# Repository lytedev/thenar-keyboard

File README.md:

# Thenar

A column-staggered, fully-wireless split keyboard with scrollwheels — 56 keys (28 per half + thumb cluster). Choc-spaced, hotswap, Nice!Nano + ZMK.

## Repositories

- **Primary**: <https://git.lyte.dev/lytedev/thenar-keyboard>
- **Mirror (GitHub)**: <https://github.com/lytedev/thenar-keyboard>
- **Sibling model**: [hypothenar](https://git.lyte.dev/lytedev/hypothenar-keyboard) — the pick-and-place (JLCPCB PCBA) sibling: same layout, completely different electronics ([GitHub mirror](https://github.com/lytedev/hypothenar-keyboard))

- Choc-spaced, hot-swappable
- Scrollwheel (`EVQWGD001`) on both sides
- Strong pinky stagger (0.66) and a 5 deg. pinky splay
- Fully wireless built for Nice!Nano + ZMK (no TRRS jack)
- Nice!View support (5 pin connector)
- Reversible PCB
- 3d printable magnetic case, switchplate and MCU cover

## Gallery

TODO: Take photos of the assembled Thenar and add them here.

## Firmware

Natively supports [ZMK](https://zmk.dev/). Build + flash via the flake:

```sh
nix build .#firmware             # both halves
nix run .#flash -- left          # build + flash (double-tap reset when prompted)
nix run .#flash -- right
```

The shield definition + keymap live in [`config/`](./config/).
See `config/README.md` for the full firmware development workflow,
including hash-pinning the Zephyr SDK on first build.

## Build guide

[see the docs](./docs/) — [build](./docs/build.md), [routing](./docs/routing.md). Both are LLM-drafted and unverified; treat them as starting points until someone has built and routed a Thenar end-to-end.

## Development

The build has two phases:

1. **Ergogen produces a scaffold** — KiCad PCBs with all the footprints
   placed and nets assigned, but **no copper routing**. This is the
   starting point.
2. **A human routes the scaffold in KiCad by hand** and commits the
   result to `thenar/routed/`. Gerbers are then exported from the
   committed routed file, not from the ergogen scaffold.

This is unavoidable: ergogen is a layout generator, not an autorouter, and
a useful keyboard PCB needs every net wired up by hand to fit two layers.

### Flake packages

```sh
nix build .#scaffold          # ergogen -> KiCad PCBs (UNROUTED, for hand-routing)
nix build .#gerbers           # gerbers from thenar/routed/keyboard.kicad_pcb
nix build .#gerbers-zip       # ^^ zipped, ready to upload to JLCPCB etc. (default)
nix build .#switchplate-step  # STEP model of the switchplate (1.2mm)
nix flake check               # verifies thenar/routed/ placement matches scaffold
```

Each `result` symlink points at the artifact in `/nix/store`. For an
interactive shell with `ergogen`, `kicad-cli`, and `zip` available:

```sh
nix develop
```

### The two paths to fab-ready gerbers

- **Use the committed routed PCB.** `nix build .#gerbers-zip` and upload
  the result. This is the default path and the only one that has a chance
  of working without you doing any routing yourself.
- **Route your own.** Run `nix build .#scaffold`, open
  `result/pcbs/keyboard.kicad_pcb` in KiCad, route every net, save the
  routed file over `thenar/routed/keyboard.kicad_pcb`, then
  `nix build .#gerbers-zip`. If you fork the repo, commit your routed
  PCB so anyone using your fork gets it for free.

`nix flake check` runs `check-routing-drift`, which compares footprint
placement between the freshly-generated scaffold and the committed
`thenar/routed/` PCB. If you edit `thenar/ergogen/config.yaml` without
re-merging into the routed file, this check will fail loudly.

## License

MIT — see [LICENSE](LICENSE).

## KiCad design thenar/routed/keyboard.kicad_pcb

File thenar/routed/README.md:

# Routed PCB

This directory holds the **manually-routed** KiCad PCBs that gerbers are built
from. Ergogen places footprints and assigns nets, but does not route copper —
that step has to be done by hand in KiCad. The result of that hand-routing
lives here and is committed.

## Workflow

1. `nix build .#pcbs` produces the ergogen scaffold (footprints + nets, no
   traces) at `result/pcbs/keyboard.kicad_pcb`.
2. The first time, that scaffold is copied verbatim into this directory as a
   seed. You then open it in KiCad and route the traces by hand. Commit the
   routed file.
3. `nix build .#gerbers` reads the routed file *from here* — not from the
   ergogen output — and produces fabricatable gerbers.
4. If you edit `thenar/ergogen/config.yaml` (e.g. moving a key, adding a
   footprint), the ergogen scaffold and this routed file go out of sync.
   Run `nix flake check` (or `nix build .#check-routing-drift`) to catch
   that — it compares footprint placement between the freshly-generated
   scaffold and this committed PCB. When drift is detected, you need to
   merge the new footprint placement back into the routed PCB in KiCad
   (KiCad can do this incrementally via "Update PCB from Schematic" style
   workflows, but with ergogen the simplest path is usually: open the new
   scaffold, copy your routing over from the old routed file, and re-save).

## Current state

> **⚠️ Currently unrouted.** The files here are a verbatim copy of the
> ergogen output. They will produce empty/unusable gerbers until someone
> opens them in KiCad and routes the traces. Do **not** order PCBs from
> the current gerber output.

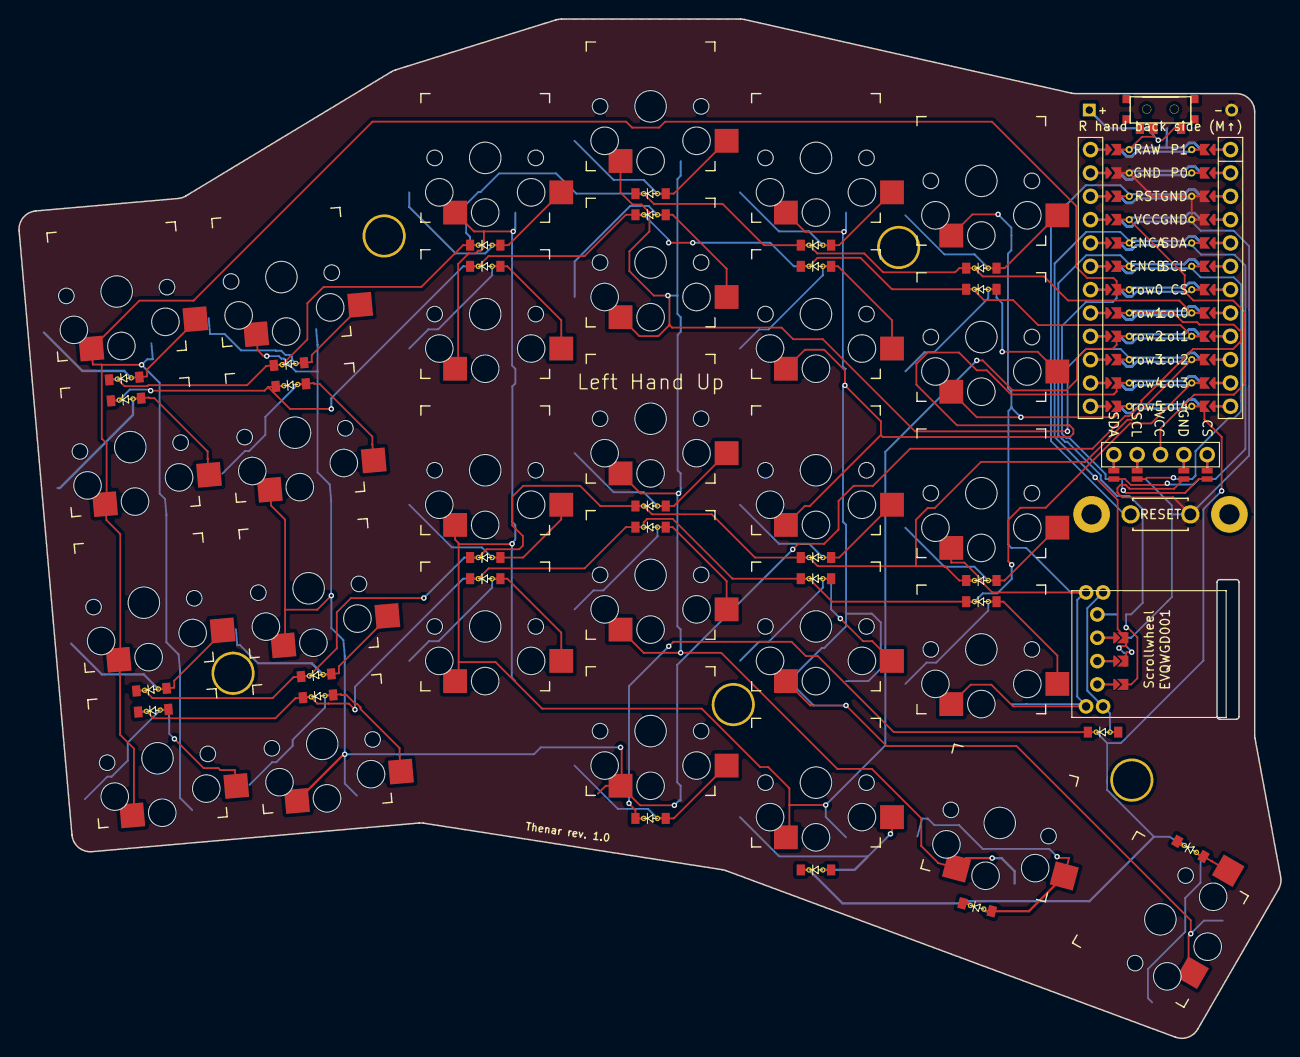
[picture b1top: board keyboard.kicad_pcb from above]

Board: 2 copper layers, 137.3 x 110.9 mm, 74 parts (0 on the bottom side), 54 nets.

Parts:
D1, D2, D3, D4, D5, D6, D7, D8, D9, D10, D11, D12, D13, D14, D15, D16, D17, D18, D19, D20, D21, D22, D23, D24, D25, D26, D27, D28, D29: ComboDiode
DISP1: display_nice_view
J1, J2, J3, J4, J5, J6: Jumper
MCU1: mcu_nice_nano
S1, S2, S3, S4, S5, S6, S7, S8, S9, S10, S11, S12, S13, S14, S15, S16, S17, S18, S19, S20, S21, S22, S23, S24, S25, S26, S27, S28: PG1350
T1: SPDT_C128955
_1: ResetSW
_2, _3, _4, _5, _6, _7, _8: Hole

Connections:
CS: DISP1.14, DISP1.24, MCU1.107
DISP1_1: DISP1.1, DISP1.10, DISP1.23
DISP1_2: DISP1.2, DISP1.11, DISP1.22
DISP1_4: DISP1.4, DISP1.12, DISP1.21
DISP1_5: DISP1.5, DISP1.13, DISP1.20
ENCA: J3.2, J6.2, MCU1.120
ENCB: J1.2, J4.2, MCU1.119
GND: DISP1.15, DISP1.25, J2.2, J5.2, MCU1.103, MCU1.104, MCU1.123, _1.2
RAW: MCU1.124, T1.2
RST: MCU1.122, _1.1
SCL: DISP1.16, DISP1.26, MCU1.106
SDA: DISP1.17, DISP1.27, MCU1.105
VCC: DISP1.3, MCU1.121
col0: D2.1, D4.1, D6.1, D9.1, D12.1, D14.1, MCU1.108
col1: D17.1, D19.1, D21.1, D23.1, D25.1, D27.1, MCU1.109
col2: D1.1, D3.1, D5.1, D8.1, D11.1, D13.1, MCU1.110
col3: D16.1, D18.1, D20.1, D22.1, D24.1, D26.1, MCU1.111
col4: D7.1, D10.1, D15.1, D28.1, D29.1, MCU1.112
index_bottom: D24.2, S19.2
index_home: D11.2, S20.2
index_mod: D10.2, S18.2
index_num: D12.2, S22.2
index_top: D25.2, S21.2
inner_bottom: D26.2, S23.2
inner_home: D13.2, S24.2
inner_num: D14.2, S26.2
inner_top: D27.2, S25.2
layer_cluster: D15.2, S27.2
middle_bottom: D22.2, S14.2
middle_home: D8.2, S15.2
middle_mod: D7.2, S13.2
middle_num: D9.2, S17.2
middle_top: D23.2, S16.2
outer_bottom: D16.2, S1.2
outer_home: D1.2, S2.2
outer_num: D2.2, S4.2
outer_top: D17.2, S3.2
pinky_bottom: D18.2, S5.2
pinky_home: D3.2, S6.2
pinky_num: D4.2, S8.2
pinky_top: D19.2, S7.2
ring_bottom: D20.2, S9.2
ring_home: D5.2, S10.2
ring_num: D6.2, S12.2
ring_top: D21.2, S11.2
row0: MCU1.118, S1.1, S2.1, S3.1, S4.1
row1: MCU1.117, S5.1, S6.1, S7.1, S8.1, S13.1
row2: MCU1.116, S9.1, S10.1, S11.1, S12.1, S18.1
row3: MCU1.115, S14.1, S15.1, S16.1, S17.1, S27.1
row4: MCU1.114, S19.1, S20.1, S21.1, S22.1, S28.1
row5: MCU1.113, S23.1, S24.1, S25.1, S26.1
space_cluster: D28.2, S28.2
sw_b: J2.1, J6.1
sw_c: J3.1, J5.1

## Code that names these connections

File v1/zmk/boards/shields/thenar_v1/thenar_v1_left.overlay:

// SPDX-License-Identifier: MIT
//
// Left half: switch-to-GPIO mapping for v1's MCP23017 expanders.
//
// The ordering must match the ergogen-derived position order encoded in
// default_transform (left.num.outer = position 0, etc.). Pin numbers
// here are pin OFFSETS on each MCP23017 (0..15), not nRF52840 GPIOs.
// MCP_A and MCP_B pin assignments mirror v1/ergogen/config.yaml's
// mcp1 / mcp2 net assignments.

#include "thenar_v1.dtsi"

&physical_layout0 {
    kscan = <&kscan_direct>;
    transform = <&default_transform>;
};

&kscan_direct {
    input-gpios
        // ---- num row (positions 0..5) - left half columns outer..inner
        = <&mcp_a 8  (GPIO_ACTIVE_LOW | GPIO_PULL_UP)>   // GPB0: outer_num
        , <&mcp_a 9  (GPIO_ACTIVE_LOW | GPIO_PULL_UP)>   // GPB1: pinky_num
        , <&mcp_a 10 (GPIO_ACTIVE_LOW | GPIO_PULL_UP)>   // GPB2: ring_num
        , <&mcp_a 11 (GPIO_ACTIVE_LOW | GPIO_PULL_UP)>   // GPB3: middle_num
        , <&mcp_a 12 (GPIO_ACTIVE_LOW | GPIO_PULL_UP)>   // GPB4: index_num
        , <&mcp_a 13 (GPIO_ACTIVE_LOW | GPIO_PULL_UP)>   // GPB5: inner_num
        // ---- top row (positions 12..17)
        , <&mcp_a 14 (GPIO_ACTIVE_LOW | GPIO_PULL_UP)>   // GPB6: outer_top
        , <&mcp_a 15 (GPIO_ACTIVE_LOW | GPIO_PULL_UP)>   // GPB7: pinky_top
        , <&mcp_a 0  (GPIO_ACTIVE_LOW | GPIO_PULL_UP)>   // GPA0: ring_top
        , <&mcp_a 1  (GPIO_ACTIVE_LOW | GPIO_PULL_UP)>   // GPA1: middle_top
        , <&mcp_a 2  (GPIO_ACTIVE_LOW | GPIO_PULL_UP)>   // GPA2: index_top
        , <&mcp_a 3  (GPIO_ACTIVE_LOW | GPIO_PULL_UP)>   // GPA3: inner_top
        // ---- home row (positions 24..29)
        , <&mcp_a 4  (GPIO_ACTIVE_LOW | GPIO_PULL_UP)>   // GPA4: outer_home
        , <&mcp_a 5  (GPIO_ACTIVE_LOW | GPIO_PULL_UP)>   // GPA5: pinky_home
        , <&mcp_a 6  (GPIO_ACTIVE_LOW | GPIO_PULL_UP)>   // GPA6: ring_home
        , <&mcp_a 7  (GPIO_ACTIVE_LOW | GPIO_PULL_UP)>   // GPA7: middle_home
        , <&mcp_b 8  (GPIO_ACTIVE_LOW | GPIO_PULL_UP)>   // GPB0: index_home
        , <&mcp_b 9  (GPIO_ACTIVE_LOW | GPIO_PULL_UP)>   // GPB1: inner_home
        // ---- bottom row (positions 36..41)
        , <&mcp_b 10 (GPIO_ACTIVE_LOW | GPIO_PULL_UP)>   // GPB2: outer_bottom
        , <&mcp_b 11 (GPIO_ACTIVE_LOW | GPIO_PULL_UP)>   // GPB3: pinky_bottom
        , <&mcp_b 12 (GPIO_ACTIVE_LOW | GPIO_PULL_UP)>   // GPB4: ring_bottom
        , <&mcp_b 13 (GPIO_ACTIVE_LOW | GPIO_PULL_UP)>   // GPB5: middle_bottom
        , <&mcp_b 14 (GPIO_ACTIVE_LOW | GPIO_PULL_UP)>   // GPB6: index_bottom
        , <&mcp_b 15 (GPIO_ACTIVE_LOW | GPIO_PULL_UP)>   // GPB7: inner_bottom
        // ---- mod row + thumbs (positions 48..51)
        , <&mcp_b 0  (GPIO_ACTIVE_LOW | GPIO_PULL_UP)>   // GPA0: middle_mod
        , <&mcp_b 1  (GPIO_ACTIVE_LOW | GPIO_PULL_UP)>   // GPA1: index_mod
        , <&mcp_b 2  (GPIO_ACTIVE_LOW | GPIO_PULL_UP)>   // GPA2: thumb_layer
        , <&mcp_b 3  (GPIO_ACTIVE_LOW | GPIO_PULL_UP)>   // GPA3: thumb_space
        ;
};

&encoder_left {
    status = "okay";
};

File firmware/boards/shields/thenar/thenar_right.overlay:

#include "thenar.dtsi"

&physical_layout0 {
    kscan = <&kscan0>;
    transform = <&default_transform>;
};

// Right half's matrix positions live in columns 6..11 of the 12-wide map.
&default_transform {
    col-offset = <6>;
};

&kscan0 {
    diode-direction = "col2row";

    // Right half's row-gpios are mirrored - the Nice!Nano sits the other way
    // around so the same physical pads land on different MCU pins.
    row-gpios
        = <&pro_micro 18 (GPIO_ACTIVE_HIGH | GPIO_PULL_DOWN)>  // col0 (num)
        , <&pro_micro 15 (GPIO_ACTIVE_HIGH | GPIO_PULL_DOWN)>  // col1 (top)
        , <&pro_micro 14 (GPIO_ACTIVE_HIGH | GPIO_PULL_DOWN)>  // col2 (home)
        , <&pro_micro 16 (GPIO_ACTIVE_HIGH | GPIO_PULL_DOWN)>  // col3 (bottom)
        , <&pro_micro 10 (GPIO_ACTIVE_HIGH | GPIO_PULL_DOWN)>  // col4 (mod + thumb + scrollwheel)
        ;

    col-gpios
        = <&pro_micro 9 GPIO_ACTIVE_HIGH>  // row0 (outer)
        , <&pro_micro 8 GPIO_ACTIVE_HIGH>  // row1 (pinky)
        , <&pro_micro 7 GPIO_ACTIVE_HIGH>  // row2 (ring)
        , <&pro_micro 6 GPIO_ACTIVE_HIGH>  // row3 (middle)
        , <&pro_micro 5 GPIO_ACTIVE_HIGH>  // row4 (index)
        , <&pro_micro 4 GPIO_ACTIVE_HIGH>  // row5 (inner)
        ;
};

&encoder_right {
    status = "okay";
};

&pinctrl {
    spi0_default: spi0_default {
        group1 {
            psels = <NRF_PSEL(SPIM_SCK, 0, 29)>,
                <NRF_PSEL(SPIM_MOSI, 0, 31)>,
                <NRF_PSEL(SPIM_MISO, 0, 25)>;
        };
    };
    spi0_sleep: spi0_sleep {
        group1 {
            psels = <NRF_PSEL(SPIM_SCK, 0, 29)>,
                <NRF_PSEL(SPIM_MOSI, 0, 31)>,
                <NRF_PSEL(SPIM_MISO, 0, 25)>;
            low-power-enable;
        };
    };
};

nice_view_spi: &spi0 {
    compatible = "nordic,nrf-spim";
    pinctrl-0 = <&spi0_default>;
    pinctrl-1 = <&spi0_sleep>;
    pinctrl-names = "default", "sleep";
    cs-gpios = <&pro_micro 19 GPIO_ACTIVE_HIGH>;
};

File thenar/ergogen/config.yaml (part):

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          to: "{{row_net}}"
        adjust:
          shift: [-5, -9]
      # B-side mount: pin order is A=ENCB, B=GND, C=ENCA. (D=unused.)
      jumper_sw_left_encb:
        what: jumper
        where: [scrollwheel]
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        adjust:
          rotate: 90
          shift: [-3, -1.27]
      # F-side mount: pin order is reversed - D=ENCB, C=GND, B=ENCA. (A=unused.)
      jumper_sw_right_encb:
        what: jumper
        where: [scrollwheel]
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          CS: CS
      # ===================================================================
      # rev2 power wiring (see docs/battery-and-power.md). rev1 (frozen at
      # git tag hw-rev1) wired battery+ -> slider -> the nice!nano RAW pin,
      # which broke battery sensing AND USB charging (on the v2 both live on
      # B+/B-, not RAW). rev2 fixes it:
      #
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
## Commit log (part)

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2025-02-24 Update README.md
    typo?
2025-05-25 doc: add link to zmk module repository
2026-05-14 feat: fork to thenar keyboard
    Rename project from corax to thenar (a 56-key variant adding a num-row key
    to the top of each outer column).
    - Remove corax54/ and corax56/ variants
    - Remove corax-specific images, build guide, and 3d/gerber artifacts
    - Add thenar/ergogen config (corax54 base + outer column num row unskipped,
    outline extended to cover the new key)
2026-05-14 docs: rewrite build guide based on upstream corax guide
    Replaces my earlier from-scratch draft. The new version is paraphrased
    from the real upstream corax build guide with counts (28 hotswaps + 29
    diodes per side) and naming adjusted for thenar. Clearly labelled as
    LLM-generated and unverified.
    Also drops the zmk-config submodule (pointed at the upstream
    corax-zmk-config repo, irrelevant for thenar) and its .gitmodules entry.
2026-05-14 feat: split scaffold/routed phases for the PCB build
    Ergogen produces footprints + nets but no copper traces. Manual KiCad
    routing is unavoidable, so model that explicitly:
    - thenar/routed/ holds the hand-routed PCB (committed). Seeded as a
    verbatim copy of the scaffold; clearly marked as unrouted until someone
    actually routes it.
    - .#scaffold (was .#pcbs) produces the ergogen scaffold for hand-routing
2026-05-14 docs: add routing guide and link from build guide
    Step-by-step for opening the scaffold in KiCad, setting design rules,
    routing order, verifying with nix flake check, and committing. Clearly
    marked as LLM-generated and unverified.
2026-05-14 docs: use pcbnew instead of kicad launcher in routing guide
    The kicad launcher requires a .kicad_pro project file, which ergogen
    does not emit. pcbnew opens the bare .kicad_pcb directly.
2026-05-14 feat: clarify reversible-PCB orientation with 'up'/'down' instead of 'front'/'back'
    Silkscreen: 'Left Hand Front' / 'Right Hand Front' -> 'Left Hand Up' /
    'Right Hand Up'. 'Front' was overloaded with the keyboard sense of 'row
    closest to the user' and obscured what the label actually means: which
    face of the reversible PCB ends up pointing toward the user's fingers.
    - Rename text in thenar/ergogen/config.yaml
    - Rewrite build.md to use 'up side' / 'down side' throughout
2026-05-14 fix(scaffold): use KiCad's own demo as .kicad_pro template
    My handwritten minimal kicad_pro was too sparse - KiCad 10's launcher
    opened it but showed 'Empty project' because it could not auto-discover
    the sibling .kicad_pcb. The launcher needs the full schema (~12
    top-level sections including pcbnew, schematic, libraries, sheets,
    text_variables, etc).
    Approach: copy KiCad's own ecc83 demo .kicad_pro as a template and
2026-05-14 feat(scaffold): auto GND pour + title-block via pcbnew Python
    Two pcbnew Python passes wired into the scaffold derivation:
    1. Title block populated (Title=Thenar, Company=lytedev, Rev=1.0,
    comments with repo link + description). Previously KiCad showed
    placeholder 'Unknown' and 'keyboard'.
    2. F.Cu + B.Cu GND filled zones added covering the board outline. This
    means GND does not need to be hand-routed: every GND-net pad ties
2026-05-14 feat(ergogen): close the outline polygon at the outer-num corner
    The outline definition added matrix_outer_num top-LEFT followed by top-RIGHT
    between outer_top and pinky_num. Because pinky_num top-left is slightly LEFT
    of outer_num top-right (pinky column is +1kx, but the polygon shift offsets
    collapse the gap to under 2mm), the polygon backtracks at that corner. With
    fillet=2 ergogen produces an outline with a non-closing gap there, breaking
    DSN export and tripping KiCad's invalid_outline DRC check.
2026-05-14 feat(flake): wire freerouting integration as .#routed-auto
    Found the two things that were silently breaking pcbnew.ExportSpecctraDSN
    by binary-searching footprints:
    - text.js emits a 'footprint' with zero pads (silkscreen-text only)
    - battery.js reuses 'lib:niceview_headers' as its KiCad module name
    DSN export aborts on either. autoroute.py now strips them from a working
    copy before DSN export, runs freerouting, and re-applies the routing
2026-05-14 fix(autoroute): split pcbnew calls into subprocesses + strip GND planes
    Two stabilizations to the autoroute pipeline:
    1. KiCad's swig pcbnew bindings segfault if you do LoadBoard + Export
    then later LoadBoard + Import + Save in the same Python process.
    Refactor autoroute.py so the export and import phases each run in
    their own subprocess (the script re-invokes itself with --export-dsn
    and --import-ses flags). The orchestrator process only does the
2026-05-14 feat(ergogen): give scrollwheel pads unique local nets
    The encoder pads A/B/C/D were assigned hybrid net names (ENCB_undef,
    GND_ENCA, ENCA_GND, undef_ENCB) - one piece of copper carrying two
    different signals depending on which side of the reversible PCB the
    encoder is mounted on. Freerouting can't autoroute these because the
    'net' identity is ambiguous.
    Same fix pattern as the Nice!Nano migration, but at the config level
2026-05-14 feat(autoroute): use Global+Sequential strategy
    freerouting defaults (Greedy+Prioritized) plateau quickly. Switching to
    Global+Sequential produces identical final results but with cleaner
    behavior - no NullPointerException warnings on first-pass attempts, and
    freerouting actually completes the requested pass count instead of
    bailing early on score-improvement heuristics.
    This does NOT solve the underlying autoroute problem: the design still
2026-05-14 pcb: hand-route the keyboard
    DRC: 0 unconnected items. Remaining DRC warnings are all pre-existing
    cosmetic issues from the upstream corax design (silk-over-copper from
    labels under the Nice!Nano body, solder-mask-bridge between adjacent
    LED/diode pads, intentionally-tight 0.1527mm clearance between solder
    jumper bridge pads on J1-J6, one stray screw-hole/switch-pad overlap
    on S26 from the original layout).
2026-05-18 feat(autoroute): freerouting v2.2.4 + config-driven options
    nixpkgs ships freerouting 2.2.1, which has a multithreaded race that
    deterministically crashes pass #1 with NullPointerException on our DSN.
    Pull v2.2.4 directly via fetchurl + wrap with temurin-jre-bin-25
    (freerouting compiled with Java 25). Drop this when nixpkgs catches up.
    v2.2.4 stability fixes resolve the crash. Also exposes config knobs we
    need that weren't present in 2.2.1's defaults:
2026-05-18 docs(routing): document autoroute findings and hybrid workflow
    Replace the speculative 'design-dependent' autoroute section with
    concrete numbers from the actual runs:
    - ~91% routed, ~23 nets typically unrouted
    - Identifies which nets get stuck (col4, matrix rows, sw_*)
    - Documents the via-count gap (102 human vs 43 autoroute) and why
    via_costs tuning helps marginally but not enough
2026-05-18 pcb: re-route from autoroute baseline -- 44 vias (was 102)
    Restarting from the freerouting v2.2.4 autoroute output and finishing
    the ~25 unrouted nets by hand. Net result vs the from-scratch hand
    route: same 0 unconnected items, ~2% longer total trace length, but
    less than half the vias.
    DRC: 0 unconnected. Remaining warnings are the same pre-existing
    cosmetic issues from the upstream design (silk-over-copper, the
2026-05-18 feat(flake): nix build .#firmware + nix run .#flash -- (left|right)
    Wires zmk-nix (https://github.com/lilyinstarlight/zmk-nix) into the
    flake to build ZMK firmware locally without GitHub Actions or a
    separate west toolchain install. Adds:
    - packages.firmware - both halves' .uf2 in one derivation
    - packages.firmware-left - just the left .uf2
    - packages.firmware-right - just the right .uf2
2026-06-01 docs: track v1.0 deviations - scrollwheel mounting peg has no NPTH
    Builders have to trim the EVQWGD001's plastic alignment peg before
    the encoder will seat flush. The footprint provides electrical pads
    and an Edge.Cuts body slot but no non-plated through-hole for the peg.
    v2 should add the NPTH. Build guide already documents the trim
    workaround. Logging here so the fix doesn't get lost across PCB revs.
2026-06-01 docs(v1): use JLCPCB programming service + lock MCP23017 choice
    Update v1-design.md with two decisions:
    - Bootloader: pay JLCPCB to flash the Adafruit nRF52 bootloader during
    PCBA (~5-30 for 2 boards) instead of DIY SWD programmer. Cheaper at
    this scale and saves manual flash step. Keep SWD pads on the PCB for
    debug/recovery.
    - I/O expander: confirm MCP23017 over PCA9555A. The 1 uA standby
2026-06-01 docs(v1): drop reversibility, two separate PCB designs
    PCBA economics flip the reversibility tradeoff. Hand-soldering paid for
    itself by sharing one PCB SKU; PCBA pays for duplicate footprints and
    jumper bridges regardless. Plus the discrete-chip BOM multiplies the
    jumper count vs rc1 (now also needs jumpers around USB-C, charge IC,
    I/O expander reset, etc.).
    Plan: one ergogen config with mirror directive, emits thenar-left.kicad_pcb
2026-06-01 docs(v1): correct BOM from LCSC verification pass
    My first-pass BOM had wrong C-numbers for almost every IC (the LCSC
    catalogue numbers I cited pointed at unrelated resistors and ADCs).
    Verified actual part numbers against JLCPCB's catalogue and updated.
    Corrected parts:
    - U1 nRF52840: C840628 -> C190794 (Extended)
    - E1 antenna: C503520 -> C2917717 (Extended)
2026-06-01 docs(v1): identify reference designs to fork from
    Researched open-source nRF52840 ZMK projects. No exact match for our
    MS88SF3 + MCP23017 combo (expected - rare combination) but four
    projects together cover everything we need:
    - Ladniy/jiran-ble-lite: PRIMARY FORK BASE - KiCad source, split,
    Holyiot 18010 module (similar to MS88SF3), CERN-OHL-P license.
    Take: split mechanics, power tree, USB-C+charge, KiCad project
2026-06-01 feat(v1): vendor reference designs + libraries
    Bring in the building blocks identified in the reference-design research:
    - v1/ref-designguide-schematic/: ebastler/zmk-designguide (CERN-OHL-P).
    Tested wireless-keyboard schematic with USB-C+ESD, TP4056 charge IC,
    XC6206 LDO, and three nRF52840 module options. The reference for our
    power tree.
    - v1/lib/kleeb/: crides/kleeb (MIT). Only public source of the MS88SF3
2026-06-02 feat(v1): ergogen footprint wrappers for power+IO chips
    Hand-written ergogen JS wrappers for the smaller parts in v1's BOM:
    - xc6206.js: XC6206 LDO (SOT-89-3, Basic-tier LCSC C5446)
    - tp4056.js: TP4056 LiPo charge IC (SOP-8, LCSC C382139)
    - usblc6.js: USBLC6-2SC6 USB ESD (SOT-23-6, LCSC C7519, optional)
    - mcp23017.js: MCP23017 I/O expander (SOIC-28W, LCSC C47023)
    Each takes net params (pad-to-net) and emits a kicad_pcb (module ...)
2026-06-02 feat(v1): kicad_mod->ergogen converter + MS88SF3 + USB-C footprints
    Hand-writing 64-pad MS88SF3 wrappers is tedium so wrote a script:
    v1/ergogen/footprints/_convert_kicad_mod.py
    Parses a .kicad_mod (s-expressions), extracts pads + geometry,
    emits an ergogen JS wrapper with one net param per pad number.
    Preserves silkscreen/fab graphics verbatim. Layer names get
    swapped to ${p.side}.X so the same footprint works as side=F or B.
